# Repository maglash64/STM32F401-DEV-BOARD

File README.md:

# STM32F401-DEV-BOARD
A 4-Layer Development and Evaluation board for STM32F401 MCU

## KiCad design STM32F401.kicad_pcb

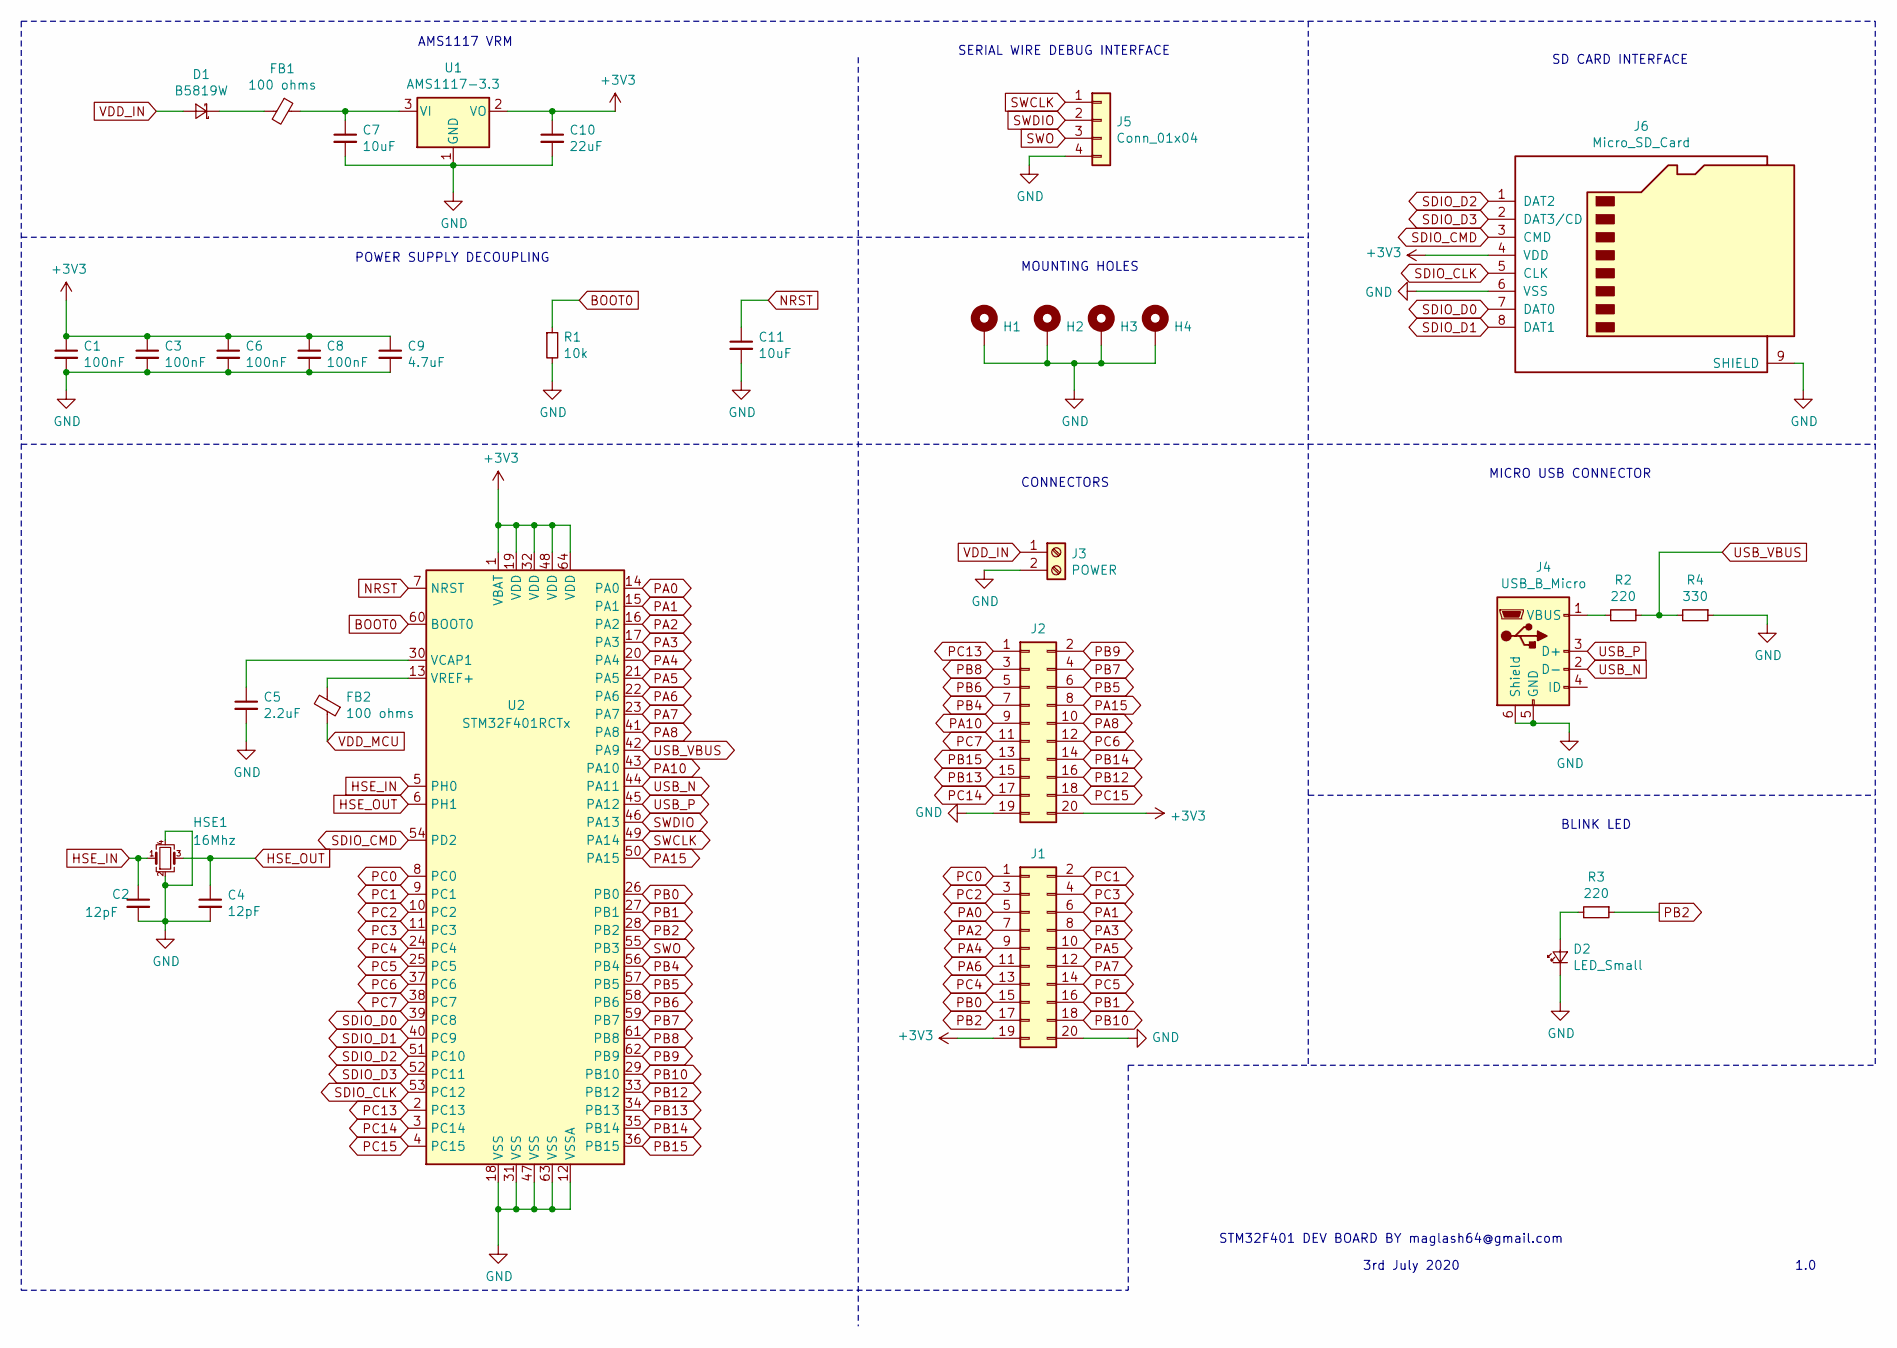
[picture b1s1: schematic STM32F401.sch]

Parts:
C1, C3, C6, C8: 100nF; C_0805_2012Metric_Pad1.15x1.40mm_HandSolder
C2, C4: 12pF; C_0805_2012Metric_Pad1.15x1.40mm_HandSolder
C5: 2.2uF; C_0805_2012Metric_Pad1.15x1.40mm_HandSolder
C7, C11: 10uF; C_0805_2012Metric_Pad1.15x1.40mm_HandSolder
C9: 4.7uF; CP_EIA-2012-12_Kemet-R_Pad1.30x1.05mm_HandSolder
C10: 22uF; CP_EIA-2012-12_Kemet-R_Pad1.30x1.05mm_HandSolder
D1: B5819W; D_SOD-123
D2: LED_Small; LED_0603_1608Metric_Pad1.05x0.95mm_HandSolder
FB1, FB2: 100 ohms; L_0805_2012Metric_Pad1.15x1.40mm_HandSolder
H1, H2, H3, H4: MountingHole_Pad; MountingHole_3.2mm_M3_Pad_Via
HSE1: 16Mhz; Crystal_SMD_3225-4Pin_3.2x2.5mm
J1, J2: Conn_02x10_Odd_Even; PinHeader_2x10_P2.54mm_Vertical
J3: POWER; TerminalBlock_bornier-2_P5.08mm
J4: USB_B_Micro; USB_Micro-B_Molex_47346-0001
J5: Conn_01x04; PinHeader_1x04_P2.54mm_Vertical
J6: Micro_SD_Card; microSD_HC_Hirose_DM3AT-SF-PEJM5
R1: 10k; R_0805_2012Metric_Pad1.15x1.40mm_HandSolder
R2, R3: 220; R_0805_2012Metric_Pad1.15x1.40mm_HandSolder
R4: 330; R_0805_2012Metric_Pad1.15x1.40mm_HandSolder
U1: AMS1117-3.3; SOT-223-3_TabPin2
U2: STM32F401RCTx; LQFP-64_10x10mm_P0.5mm

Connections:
+3V3: C1.1, C3.1, C6.1, C8.1, C9.1, C10.1, J1.19, J2.20, J6.4 (VDD), U1.2 (VO), U2.1 (VBAT), U2.19 (VDD), U2.32 (VDD), U2.48 (VDD), U2.64 (VDD)
BOOT0: R1.1, U2.60 (BOOT0)
HSE_IN: C2.1, HSE1.1, U2.5 (PH0)
HSE_OUT: C4.1, HSE1.3, U2.6 (PH1)
NRST: C11.1, U2.7 (NRST)
unnamed: C5.1, U2.30 (VCAP1)
unnamed: C7.1, FB1.1, U1.3 (VI)
unnamed: D1.1 (K), FB1.2
unnamed: D2.2 (A), R3.2
unnamed: FB2.2, U2.13 (VREF+)
unnamed: J4.1 (VBUS), R2.2
PA0: J1.5, U2.14 (PA0)
PA1: J1.6, U2.15 (PA1)
PA2: J1.7, U2.16 (PA2)
PA3: J1.8, U2.17 (PA3)
PA4: J1.9, U2.20 (PA4)
PA5: J1.10, U2.21 (PA5)
PA6: J1.11, U2.22 (PA6)
PA7: J1.12, U2.23 (PA7)
PA8: J2.10, U2.41 (PA8)
PA10: J2.9, U2.43 (PA10)
PA15: J2.8, U2.50 (PA15)
PB0: J1.15, U2.26 (PB0)
PB1: J1.16, U2.27 (PB1)
PB2: J1.17, R3.1, U2.28 (PB2)
PB4: J2.7, U2.56 (PB4)
PB5: J2.6, U2.57 (PB5)
PB6: J2.5, U2.58 (PB6)
PB7: J2.4, U2.59 (PB7)
PB8: J2.3, U2.61 (PB8)
PB9: J2.2, U2.62 (PB9)
PB10: J1.18, U2.29 (PB10)
PB12: J2.16, U2.33 (PB12)
PB13: J2.15, U2.34 (PB13)
PB14: J2.14, U2.35 (PB14)
PB15: J2.13, U2.36 (PB15)
PC0: J1.1, U2.8 (PC0)
PC1: J1.2, U2.9 (PC1)
PC2: J1.3, U2.10 (PC2)
PC3: J1.4, U2.11 (PC3)
PC4: J1.13, U2.24 (PC4)
PC5: J1.14, U2.25 (PC5)
PC6: J2.12, U2.37 (PC6)
PC7: J2.11, U2.38 (PC7)
PC13: J2.1, U2.2 (PC13)
PC14: J2.17, U2.3 (PC14)
PC15: J2.18, U2.4 (PC15)
SDIO_CLK: J6.5 (CLK), U2.53 (PC12)
SDIO_CMD: J6.3 (CMD), U2.54 (PD2)
SDIO_D0: J6.7 (DAT0), U2.39 (PC8)
SDIO_D1: J6.8 (DAT1), U2.40 (PC9)
SDIO_D2: J6.1 (DAT2), U2.51 (PC10)
SDIO_D3: J6.2 (DAT3/CD), U2.52 (PC11)
SWCLK: J5.1, U2.49 (PA14)
SWDIO: J5.2, U2.46 (PA13)
SWO: J5.3, U2.55 (PB3)
USB_N: J4.2 (D-), U2.44 (PA11)
USB_P: J4.3 (D+), U2.45 (PA12)
USB_VBUS: R2.1, R4.2, U2.42 (PA9)
VDD_IN: D1.2 (A), J3.1
VDD_MCU: FB2.1

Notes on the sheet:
STM32F401 DEV BOARD BY maglash64@gmail.com
1.0
3rd July 2020
MICRO USB CONNECTOR
BLINK LED
SD CARD INTERFACE
SERIAL WIRE DEBUG INTERFACE
MOUNTING HOLES
CONNECTORS
AMS1117 VRM
POWER SUPPLY DECOUPLING

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
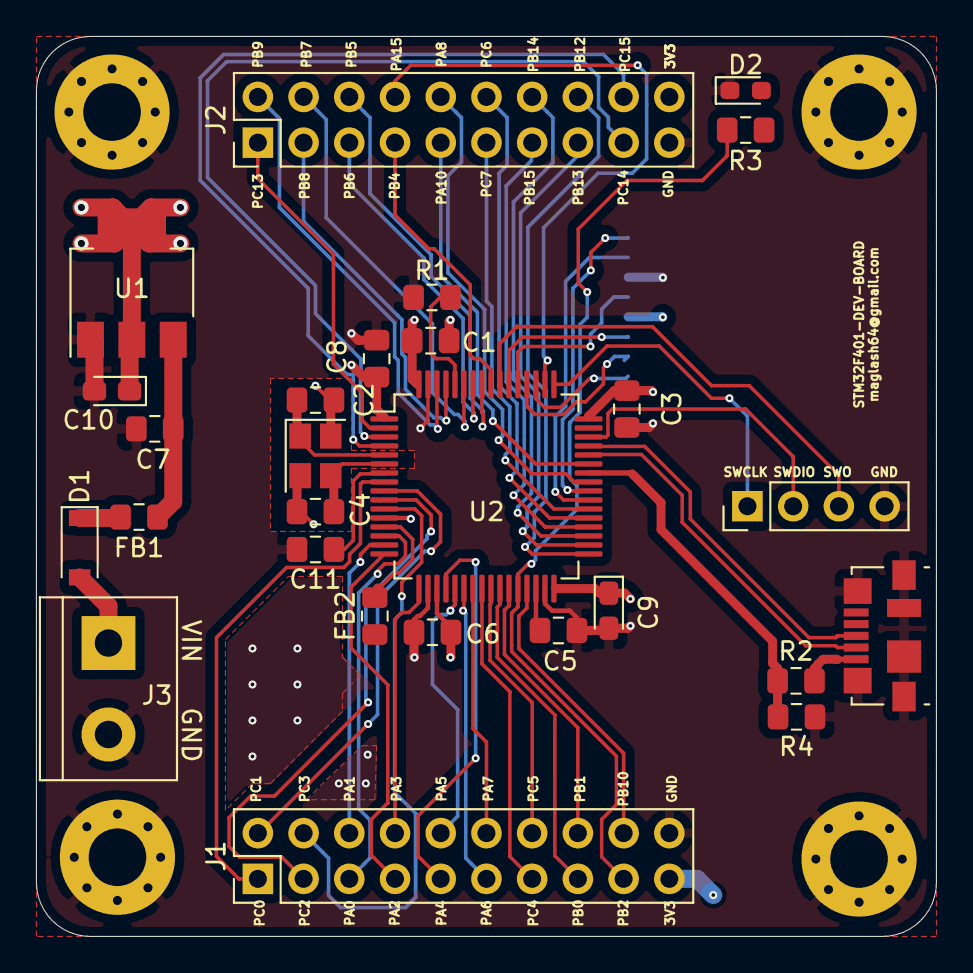
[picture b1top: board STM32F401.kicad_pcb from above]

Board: 4 copper layers, 50.0 x 50.0 mm, 32 parts (1 on the bottom side), 61 nets.

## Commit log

2020-07-04 upload
2020-07-04 created
